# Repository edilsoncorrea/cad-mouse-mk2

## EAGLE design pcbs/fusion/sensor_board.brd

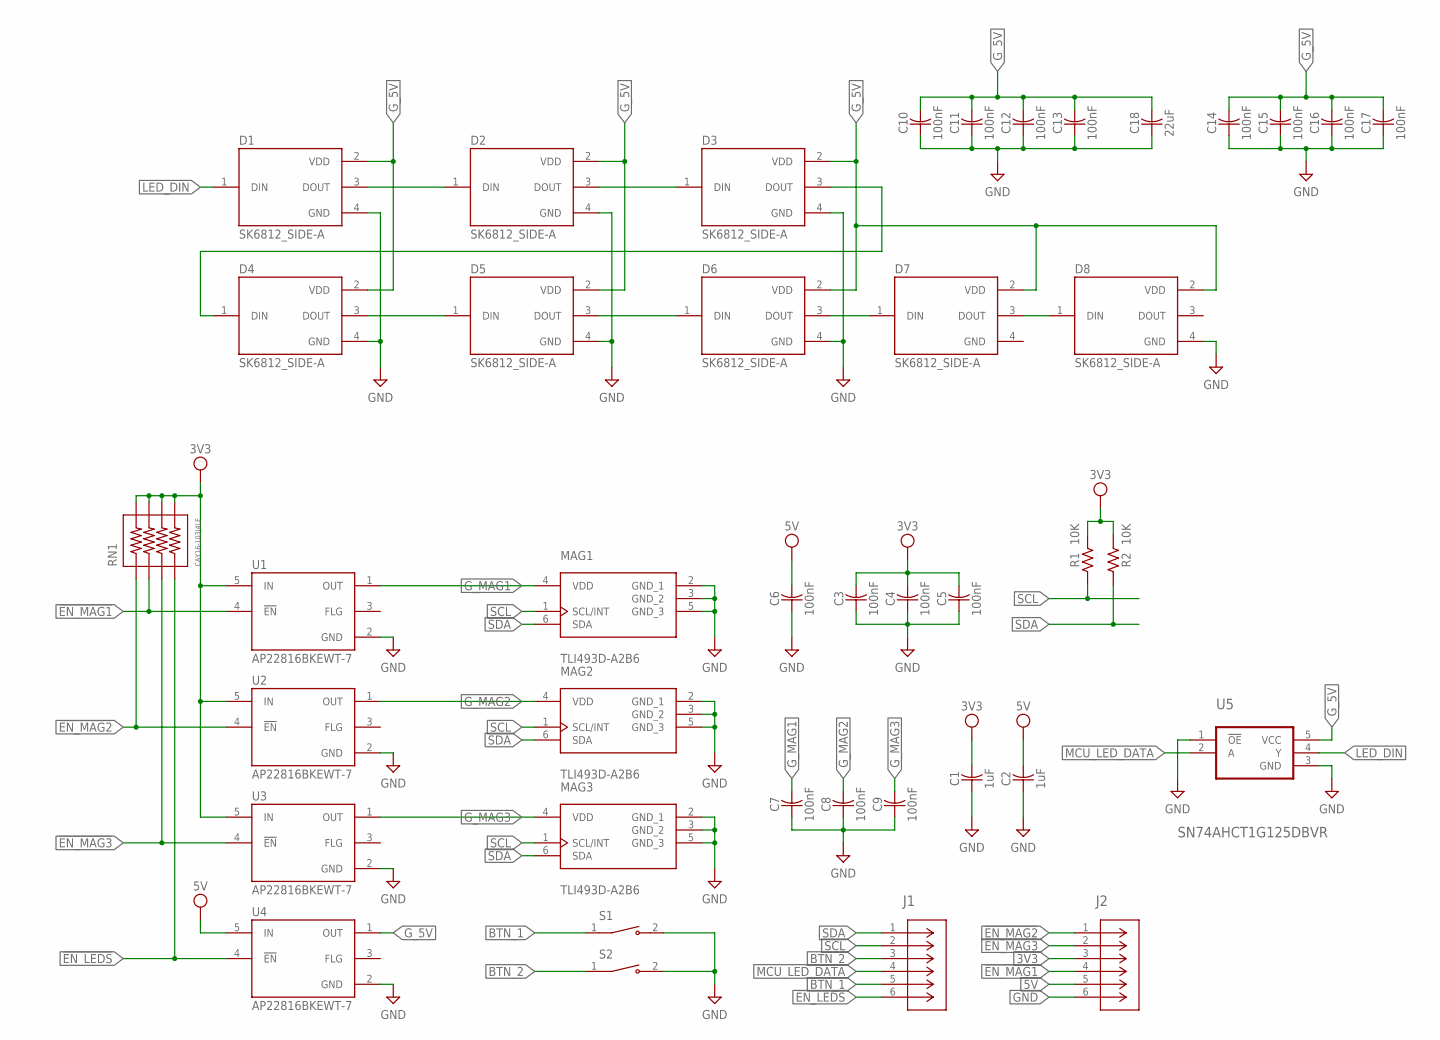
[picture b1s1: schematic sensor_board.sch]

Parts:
C1, C2: 1uF; CAPC3216X135
C3, C4, C5, C6, C7, C8, C9, C10, C11, C12, C13, C14, C15, C16, C17: 100nF; CAPC2012X110
C18: 22uF; CAPC3216X135
D1, D2, D3, D4, D5, D6, D7, D8: SK6812_SIDE-A; LED_SK6812_SIDE-A
J1, J2: NPPN032AFCN-RCCONN3X2_NPPN032AFCN-RC_SUL; CONN3X2_NPPN032AFCN-RC_SUL
MAG1, MAG2, MAG3: TLI493D-A2B6; SOP95P280X110-6N-V
R1, R2: 10K; RESC2012X65
RN1: CAY16-103J4LF; RESCAF80P320X160X60-8N
S1, S2: TS32-7-35-BK-160-RA-SMT-TR; SW_TS32-7-35-BK-160-RA-SMT-TR
U1, U2, U3, U4: AP22816BKEWT-7; SOT95P280X100-5N
U5: SN74AHCT1G125DBVR; SOT95P280X145-5N

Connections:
3V3: C1.2, C3.2, C4.2, C5.2, J2.3, R1.2, R2.2, RN1.5, RN1.6, RN1.7, RN1.8, U1.5 (IN), U2.5 (IN), U3.5 (IN)
5V: C2.2, C6.2, J2.5, U4.5 (IN)
!EN_LEDS: J1.6, RN1.4, U4.4 (!EN)
!EN_MAG1: J2.4, RN1.2, U1.4 (!EN)
!EN_MAG2: J2.1, RN1.1, U2.4 (!EN)
!EN_MAG3: J2.2, RN1.3, U3.4 (!EN)
BTN_1: J1.5, S1.1
BTN_2: J1.3, S2.1
GND: C1.1, C2.1, C3.1, C4.1, C5.1, C6.1, C7.1, C8.1, C9.1, C10.1, C11.1, C12.1, C13.1, C14.1, C15.1, C16.1, C17.1, C18.1, D1.4 (GND), D2.4 (GND), D3.4 (GND), D4.4 (GND), D5.4 (GND), D6.4 (GND), D7.4 (GND), D8.4 (GND), J2.6, MAG1.2 (GND_1), MAG1.3 (GND_2), MAG1.5 (GND_3), MAG2.2 (GND_1), MAG2.3 (GND_2), MAG2.5 (GND_3), MAG3.2 (GND_1), MAG3.3 (GND_2), MAG3.5 (GND_3), S1.2, S2.2, U1.2 (GND), U2.2 (GND), U3.2 (GND), U4.2 (GND), U5.1 (!OE), U5.3 (GND)
G_5V: C10.2, C11.2, C12.2, C13.2, C14.2, C15.2, C16.2, C17.2, C18.2, D1.2 (VDD), D2.2 (VDD), D3.2 (VDD), D4.2 (VDD), D5.2 (VDD), D6.2 (VDD), D7.2 (VDD), D8.2 (VDD), U4.1 (OUT), U5.5 (VCC)
G_MAG1: C7.2, MAG1.4 (VDD), U1.1 (OUT)
G_MAG2: C8.2, MAG2.4 (VDD), U2.1 (OUT)
G_MAG3: C9.2, MAG3.4 (VDD), U3.1 (OUT)
LED_DIN: D1.1 (DIN), U5.4 (Y)
MCU_LED_DATA: J1.4, U5.2 (A)
unnamed: D1.3 (DOUT), D2.1 (DIN)
unnamed: D2.3 (DOUT), D3.1 (DIN)
unnamed: D6.3 (DOUT), D7.1 (DIN)
unnamed: D3.3 (DOUT), D4.1 (DIN)
unnamed: D4.3 (DOUT), D5.1 (DIN)
unnamed: D5.3 (DOUT), D6.1 (DIN)
unnamed: D7.3 (DOUT), D8.1 (DIN)
SCL: J1.2, MAG1.1 (SCL/INT), MAG2.1 (SCL/INT), MAG3.1 (SCL/INT), R1.1
SDA: J1.1, MAG1.6 (SDA), MAG2.6 (SDA), MAG3.6 (SDA), R2.1

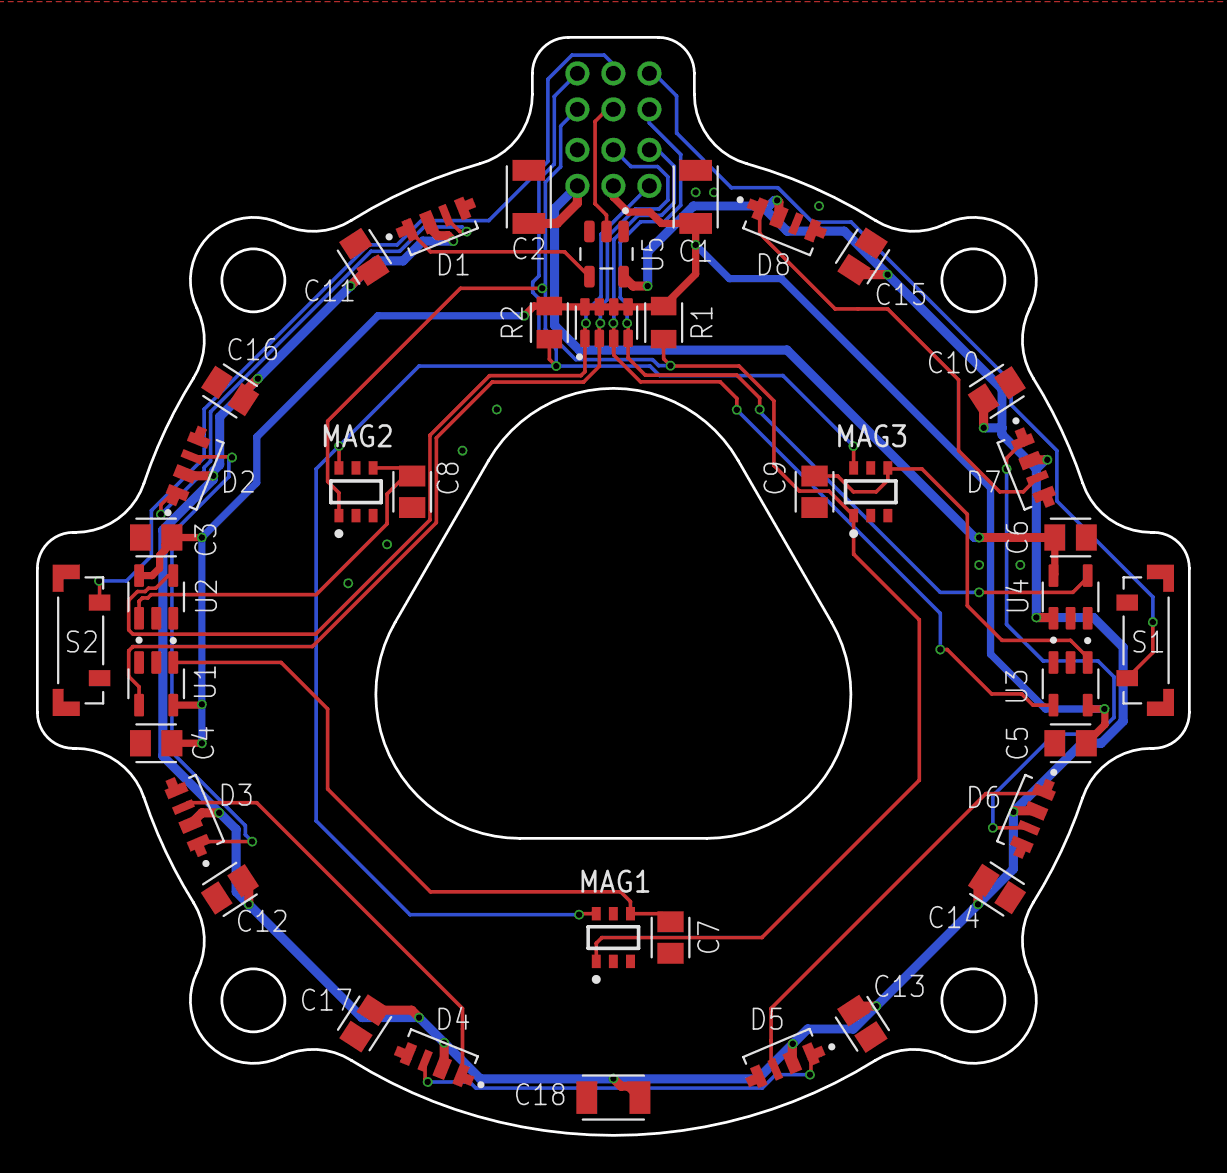
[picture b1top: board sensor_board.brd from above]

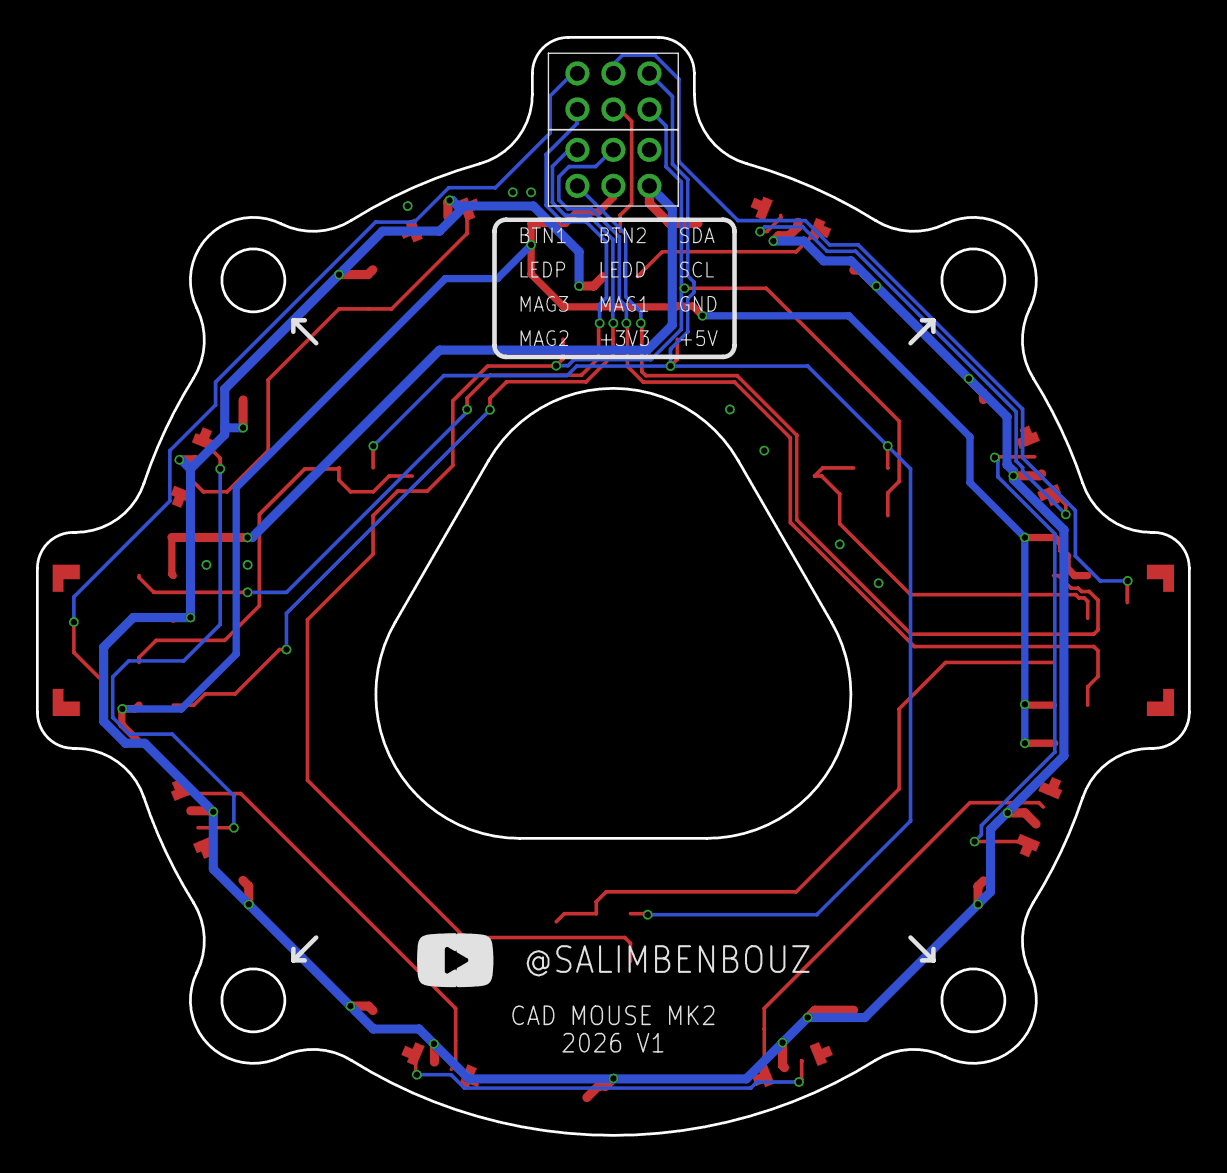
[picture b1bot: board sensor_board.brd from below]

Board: 2 copper layers, 64.0 x 61.0 mm, 41 parts (2 on the bottom side), 24 nets.

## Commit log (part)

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2026-04-16 feat: refactor motion pipeline with 5 configurable stages
    Replaces the hard-coded motion processing in MotionController with a
    modular, data-driven pipeline. All changes preserve the existing public
    API and default behavior (output is identical with default config).
    New pipeline:
    raw[9] -> baseline subtract -> matrix transform 6x9
    -> cross-axis compensation 6x6 -> gain x sign
2026-04-16 fix: set default_envs to skip native on pio run
    The native env is test-only (build_src_filter = -<*>, no entry point).
    Running 'pio run' without -e tried to build both envs, causing a
    linker failure on native. Adding default_envs = seeed_xiao_rp2040
    makes 'pio run' target only the production build.
    Tests still work via 'pio test -e native'.
2026-04-30 feat: native 3Dconnexion driver compatibility via HID protocol emulation
2026-05-04 feat: migrate sensors from TLI493D-A2B6 (gen2) to TLI493D-A1B6 (gen1)
2026-05-05 feat: invert power logic for PMOS high-side switches (LOW=ON, HIGH=OFF)
2026-05-05 feat: enable onboard NeoPixel LED (USE_ONBOARD_LED) for testing without ring
2026-05-06 feat: add SENSOR_ADDR_RETRY compile-time option for persisted I2C address recovery

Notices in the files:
parts and their libraries:
COPYRIGHT: Copyright (C) 2026 Ultra Librarian. All rights reserved.
